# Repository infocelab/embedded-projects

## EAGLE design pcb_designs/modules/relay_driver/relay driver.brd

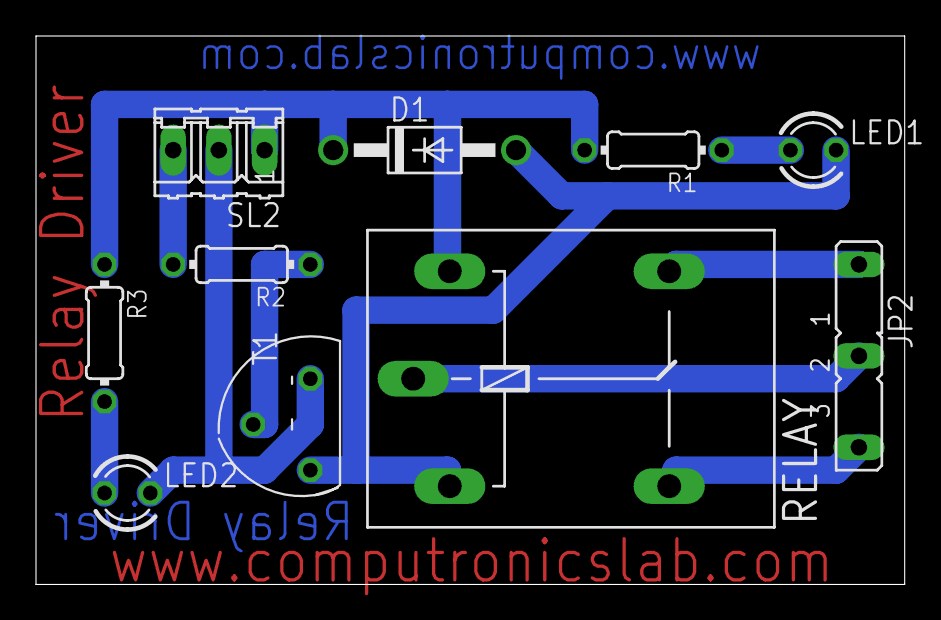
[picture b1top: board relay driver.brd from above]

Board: 2 copper layers, 48.3 x 30.5 mm, 10 parts (0 on the bottom side), 10 nets.

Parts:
D1: 1N4007; DO41-10
JP2: JP2
LED1, LED2: LED3MM
R1, R3: 330E; 0204/7
R2: 2.2K; 0204/7
RELAY: 12V; G5LE
SL2: 03P
T1: BC547; TO92

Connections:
unnamed: D1.A, LED1.K, RELAY.1, T1.3
unnamed: JP2.2, RELAY.P
unnamed: LED1.A, R1.1
unnamed: R2.1, T1.2
unnamed: LED2.K, SL2.2, T1.1
unnamed: D1.C, R1.2, R3.1, RELAY.2, SL2.1
unnamed: R2.2, SL2.3
unnamed: JP2.3, RELAY.S
unnamed: LED2.A, R3.2
unnamed: JP2.1, RELAY.O

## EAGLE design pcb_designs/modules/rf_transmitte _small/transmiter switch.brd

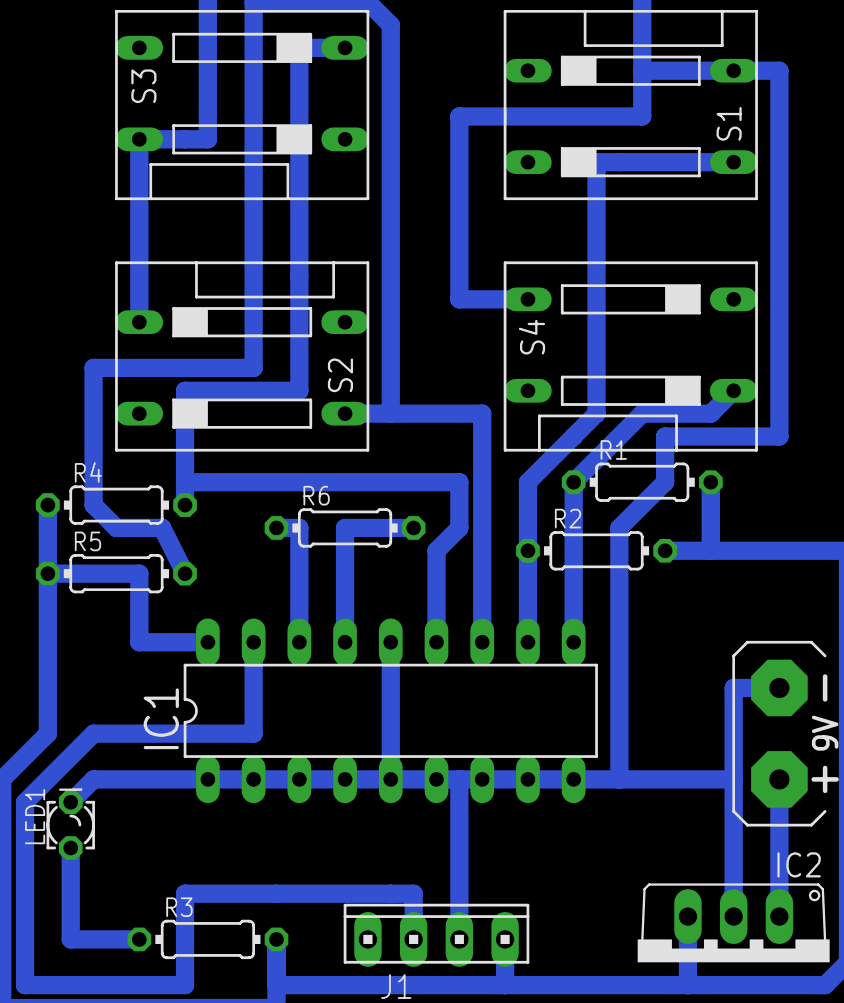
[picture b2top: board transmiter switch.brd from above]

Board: 2 copper layers, 15 parts (0 on the bottom side), 11 nets.

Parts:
G1: AB9V
IC1: HT12E; DIL18
IC2: 7805TV; TO220V
J1: transmitter; 10X04MTA
LED1: 5mm; LED_LD260
R1, R2, R4, R5: 1k; 0204/7
R3: 330E; 0204/7
R6: 1ME; 0204/7
S1: push switch 1; DS-02
S2: push switch2; DS-02
S3: push switch 3; DS-02
S4: push switch 4; DS-02

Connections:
unnamed: LED1.A, R3.1
unnamed: IC1.10, R1.1, S4.1
unnamed: IC1.11, R2.1, S1.3
unnamed: IC1.12, R5.2, S2.3
unnamed: IC1.13, R4.2, S3.2
unnamed: IC1.16, R6.1
unnamed: IC1.15, R6.2
unnamed: IC1.18, IC2.3, J1.1, R1.2, R2.2, R3.2, R4.1, R5.1
unnamed: IC1.17, J1.3
unnamed: G1.-, IC1.1, IC1.2, IC1.3, IC1.4, IC1.5, IC1.6, IC1.7, IC1.8, IC1.9, IC1.14, IC2.2, J1.2, LED1.K, S1.4, S2.1, S3.4, S4.3
unnamed: G1.+, IC2.1

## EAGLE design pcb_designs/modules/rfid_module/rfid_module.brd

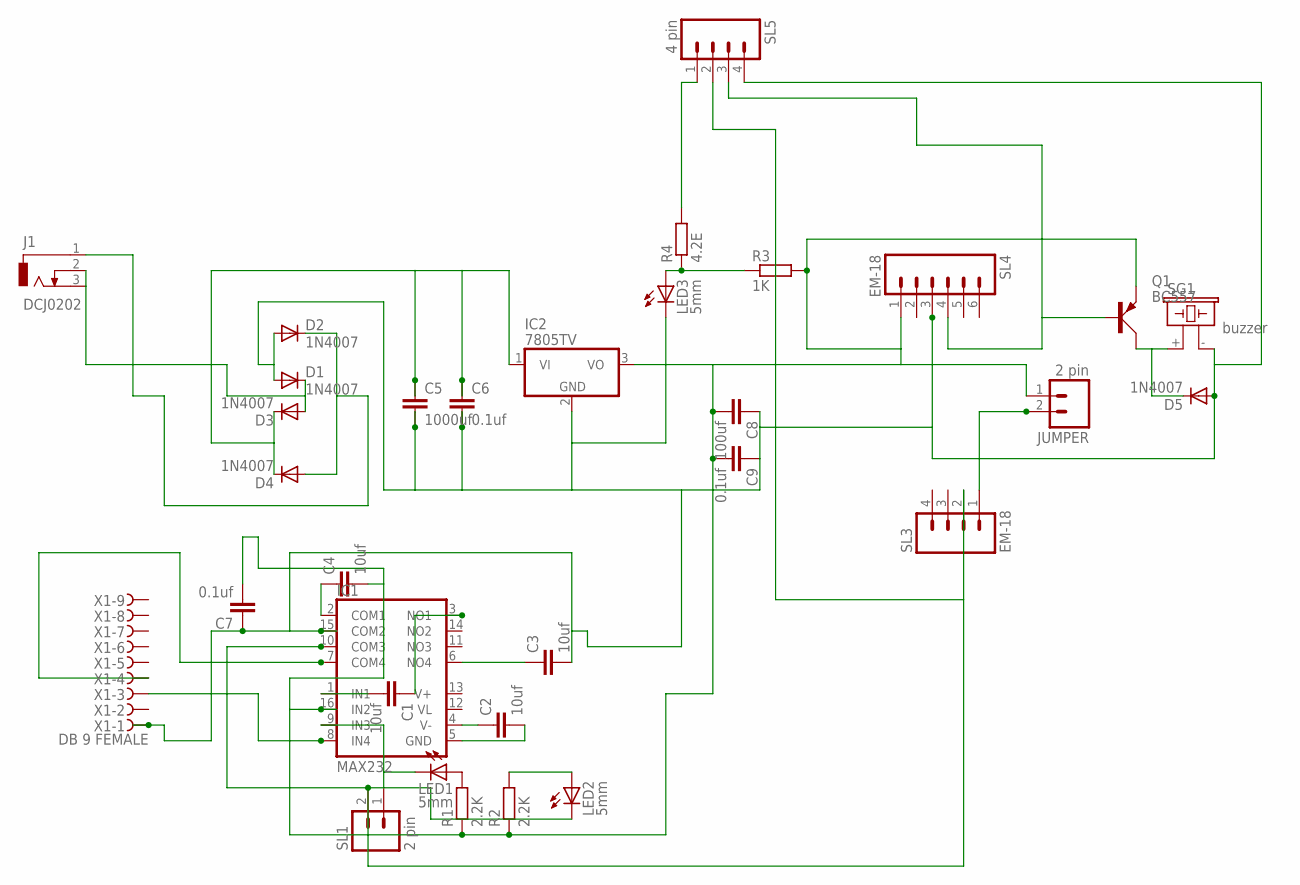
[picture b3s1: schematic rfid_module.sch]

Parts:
C1, C2, C3, C4: 10uf; C2.5-3
C5: 1000uf; C5B7.2
C6, C7, C9: 0.1uf; C2.5-3
C8: 100uf; C2.5-3
D1, D2, D3, D4, D5: 1N4007; DO41-10
IC1: MAX232; DIL16
IC2: 7805TV; TO220V
J1: DCJ0202
JUMPER: 2 pin; 02P
LED1, LED2, LED3: 5mm; LED5MM
Q1: BC557; SOT54A
R1, R2: 2.2K; 0204/7
R3: 1K; 0204/7
R4: 4.2E; 0204/7
SG1: buzzer; F/CM12P
SL1: 2 pin; 02P
SL3: EM-18; 04P
SL4: EM-18; 06P
SL5: 4 pin; 04P
X1: DB 9 FEMALE; H2M09ST

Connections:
unnamed: C1.2, IC1.1 (IN1)
unnamed: C1.1, IC1.3 (NO1)
unnamed: C2.1, IC1.4 (V-)
unnamed: C2.2, IC1.5 (GND)
unnamed: C3.1, IC1.6 (NO4)
unnamed: C4.2, C7.2, C8.2, C9.2, IC1.16 (IN2), IC2.3 (VO), JUMPER.1, Q1.E, R1.1, R2.1, R3.2, SL4.1
unnamed: C4.1, IC1.2 (COM1)
unnamed: IC1.9 (IN3), LED1.K (C), SL1.1
unnamed: IC1.8 (IN4), X1.3
unnamed: IC1.7 (COM4), X1.4
unnamed: IC1.10 (COM3), LED2.K (C), SL1.2, SL3.2, SL5.2
unnamed: LED2.A, R2.2
unnamed: C3.2, C5.2, C6.2, C7.1, C8.1, C9.1, D1.A, D2.A, D5.A, IC1.15 (COM2), IC2.2 (GND), LED3.K (C), SG1.- (2), SL4.3, SL5.4, X1.1
unnamed: C5.1, C6.1, D3.C, D4.C, IC2.1 (VI)
unnamed: D2.C, D4.A, J1.1
unnamed: LED1.A, R1.2
unnamed: D5.C, Q1.C, SG1.+ (1)
unnamed: D1.C, D3.A, J1.2, J1.3
unnamed: Q1.B, SL4.4, SL5.3
unnamed: JUMPER.2, SL3.1
unnamed: LED3.A, R3.1, R4.1
unnamed: R4.2, SL5.1
V+: IC1.13 (V+)
VL: IC1.12 (VL)

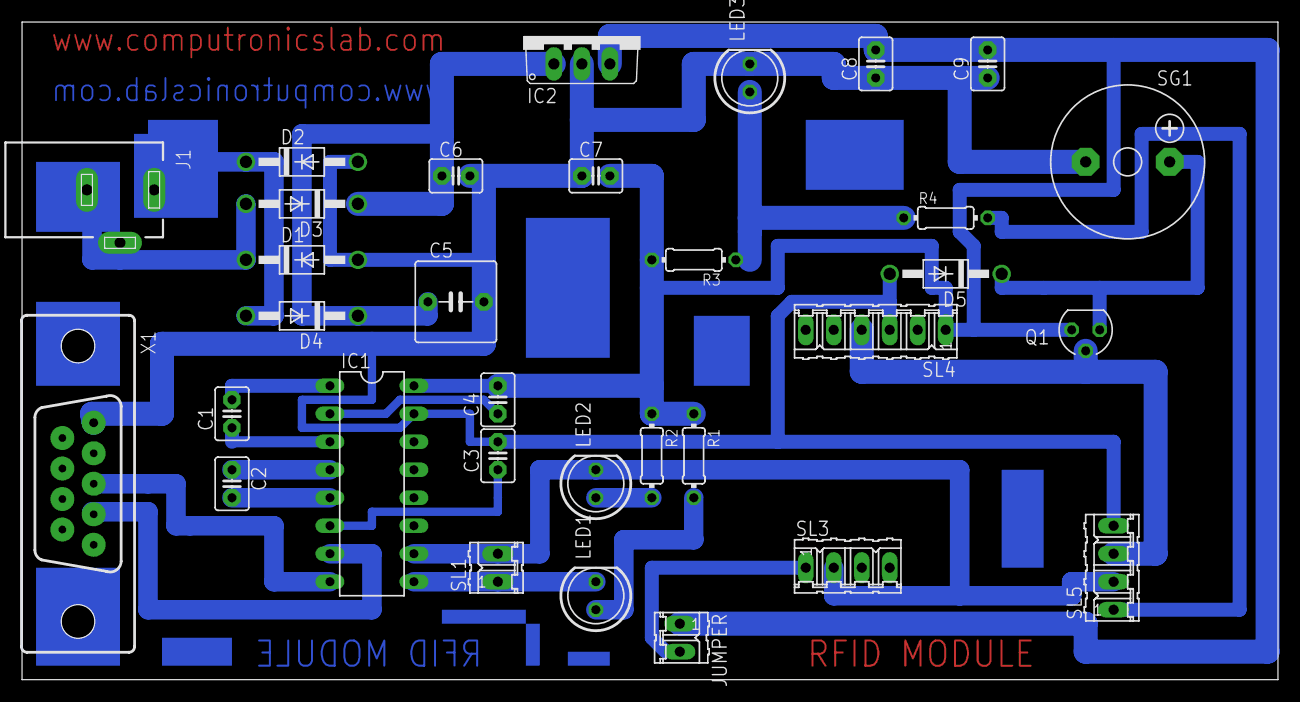
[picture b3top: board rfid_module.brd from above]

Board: 2 copper layers, 114.0 x 59.7 mm, 32 parts (0 on the bottom side), 22 nets.

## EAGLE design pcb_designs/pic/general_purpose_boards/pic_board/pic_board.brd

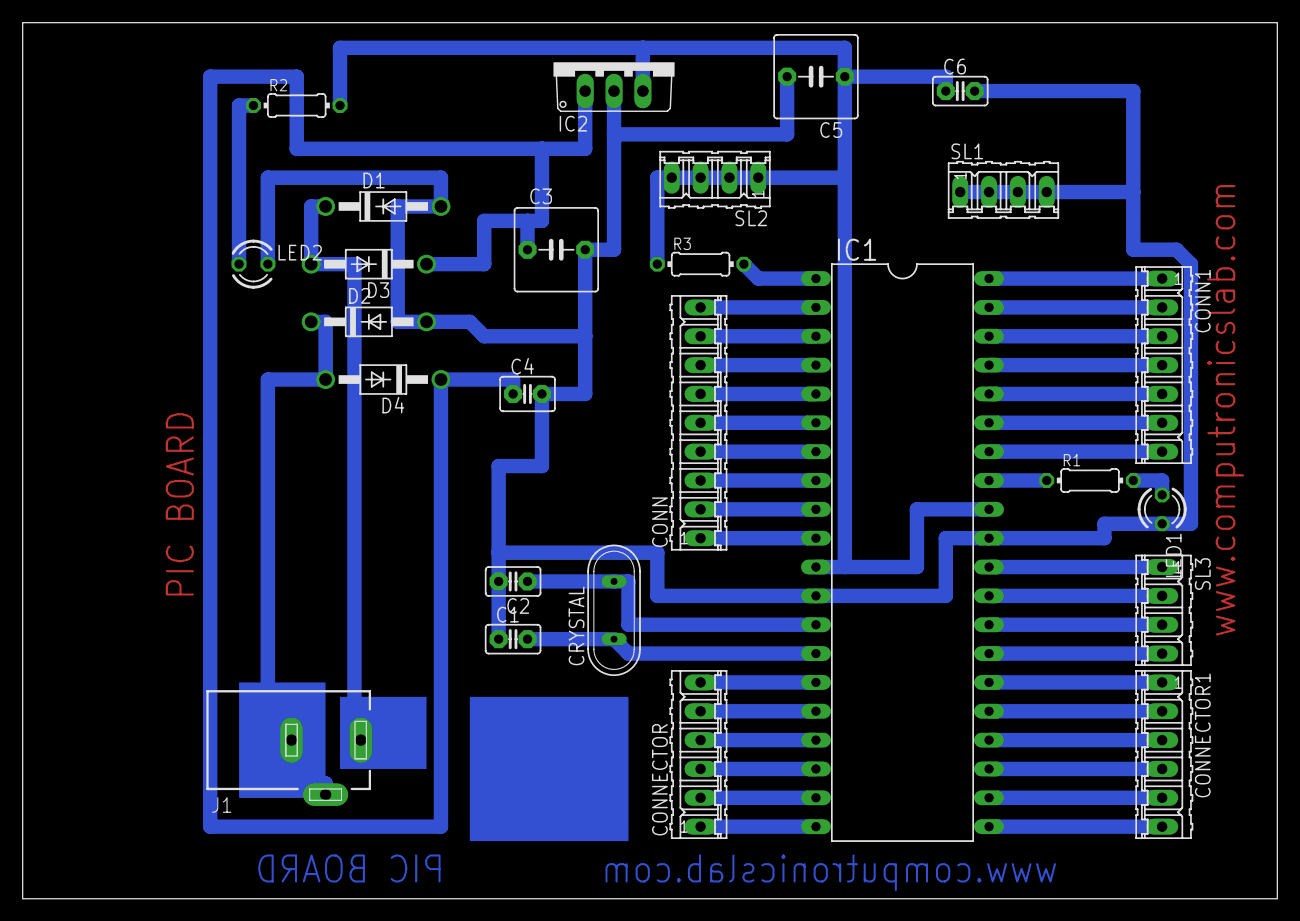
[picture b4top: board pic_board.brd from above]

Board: 2 copper layers, 110.5 x 77.1 mm, 26 parts (0 on the bottom side), 43 nets.

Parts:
C1, C2, C6: 22pf; C2.5-2
C3: 1000uf; C5B7.2
C4: 0.1uf; C2.5-3
C5: 100uf; C5B7.2
CONN: 9 pin; 09P
CONN1: 7 pin; 07P
CONNECTOR, CONNECTOR1: 6 pin; 06P
CRYSTAL: 8MHZ; QS
D1, D2, D3, D4: 1N4007; DO41-10
IC1: PIC16f877a; DIL40
IC2: 7805TV; TO220V
J1: DCJ0303
LED1, LED2: 3mm; LED3MM
R1, R2: 220E; 0204/7
R3: 10K; 0204/7
SL1, SL2, SL3: 4 pin; 04P

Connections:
unnamed: C2.1, CRYSTAL.2, IC1.13
unnamed: C1.2, CRYSTAL.1, IC1.14
unnamed: LED1.A, R1.2
unnamed: CONN.1, IC1.10
unnamed: CONN.2, IC1.9
unnamed: CONN.3, IC1.8
unnamed: CONN.4, IC1.7
unnamed: CONN.5, IC1.6
unnamed: CONN.6, IC1.5
unnamed: CONN.7, IC1.4
unnamed: CONN.8, IC1.3
unnamed: CONN.9, IC1.2
unnamed: CONNECTOR.1, IC1.20
unnamed: CONNECTOR.2, IC1.19
unnamed: CONNECTOR.3, IC1.18
unnamed: CONNECTOR.4, IC1.17
unnamed: CONNECTOR.5, IC1.16
unnamed: CONNECTOR.6, IC1.15
unnamed: CONN1.1, IC1.40
unnamed: CONN1.2, IC1.39
unnamed: CONN1.3, IC1.38
unnamed: CONN1.4, IC1.37
unnamed: CONN1.5, IC1.36
unnamed: CONN1.6, IC1.35
unnamed: CONN1.7, IC1.34
unnamed: CONNECTOR1.1, IC1.26
unnamed: CONNECTOR1.2, IC1.25
unnamed: CONNECTOR1.3, IC1.24
unnamed: IC1.33, R1.1
unnamed: C3.1, C4.1, D3.C, D4.C, IC2.1
unnamed: D2.C, D4.A, J1.2, J1.3
unnamed: D1.C, D3.A, J1.1
unnamed: C5.1, C6.1, IC1.11, IC1.32, IC2.3, R2.2, R3.1, SL2.1, SL2.2, SL2.3, SL2.4
unnamed: LED2.A, R2.1
unnamed: C1.1, C2.2, C3.2, C4.2, C5.2, C6.2, D1.A, D2.A, IC1.12, IC1.31, IC2.2, LED1.K, LED2.K, SL1.1, SL1.2, SL1.3, SL1.4
unnamed: CONNECTOR1.4, IC1.23
unnamed: CONNECTOR1.5, IC1.22
unnamed: CONNECTOR1.6, IC1.21
unnamed: IC1.1, R3.2
unnamed: IC1.30, SL3.1
unnamed: IC1.29, SL3.2
unnamed: IC1.28, SL3.3
unnamed: IC1.27, SL3.4

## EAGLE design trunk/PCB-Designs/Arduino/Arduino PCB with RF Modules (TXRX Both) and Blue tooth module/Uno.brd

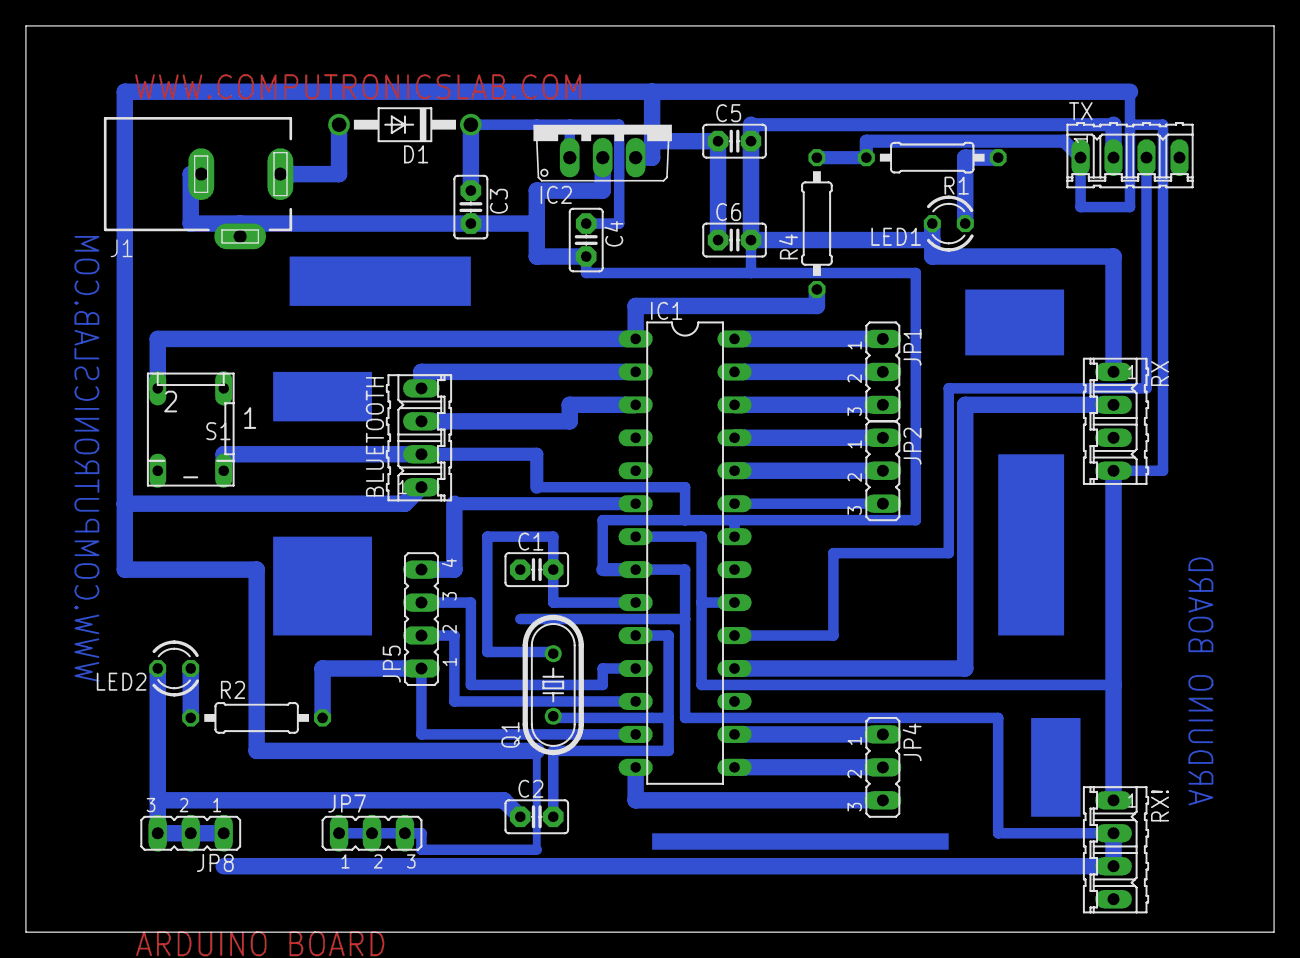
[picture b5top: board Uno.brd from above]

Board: 2 copper layers, 96.2 x 69.8 mm, 27 parts (0 on the bottom side), 26 nets.

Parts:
BLUETOOTH: 04P
C1, C2: 22pf; C2.5-2
C3: 470UF; C2.5-2
C4, C5: 0.1uf; C2.5-2
C6: 4.7uf; C2.5-2
D1: 1N4007; DO41-10
IC1: ATMEGA328; DIL28-3
IC2: 7805; TO220V
J1: DCJ0303
JP1, JP2, JP4, JP7, JP8: JP2
JP5: JP4
LED1, LED2: LED3MM
Q1: 12MHZ; HC49/S
R1: 220R; 0207/10
R2: 330R; 0207/10
R4: 10K; 0207/10
RX: 04P
RX!: 04P
S1: DP-02
TX: 04P

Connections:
unnamed: C1.2, IC1.9, Q1.2
unnamed: C2.2, IC1.10, Q1.1
unnamed: D1.A, J1.1
unnamed: BLUETOOTH.1, C5.1, C6.1, IC1.7, IC1.20, IC2.3, JP7.1, JP7.2, JP7.3, R1.2, R4.2, RX.4, RX!.1, TX.1
unnamed: BLUETOOTH.2, C1.1, C2.1, C3.2, C4.2, C5.2, C6.2, IC1.8, IC1.22, IC2.2, J1.2, J1.3, JP8.1, JP8.2, JP8.3, LED1.K, LED2.K, RX.1, RX!.2, RX!.3, S1.4, TX.2
unnamed: LED1.A, R1.1
unnamed: C3.1, C4.1, D1.C, IC2.1
unnamed: IC1.28, JP1.1
unnamed: IC1.27, JP1.2
unnamed: IC1.26, JP1.3
unnamed: IC1.25, JP2.1
unnamed: IC1.24, JP2.2
unnamed: IC1.23, JP2.3
unnamed: BLUETOOTH.4, IC1.2
unnamed: BLUETOOTH.3, IC1.3
unnamed: IC1.6, JP5.4
unnamed: IC1.12, JP5.2
unnamed: IC1.11, JP5.3
unnamed: IC1.13, JP5.1, R2.2
unnamed: IC1.14, JP4.3
unnamed: IC1.15, JP4.2
unnamed: IC1.16, JP4.1
unnamed: IC1.18, RX.2
unnamed: IC1.19, TX.3
unnamed: IC1.1, R4.1, S1.2
unnamed: LED2.A, R2.1

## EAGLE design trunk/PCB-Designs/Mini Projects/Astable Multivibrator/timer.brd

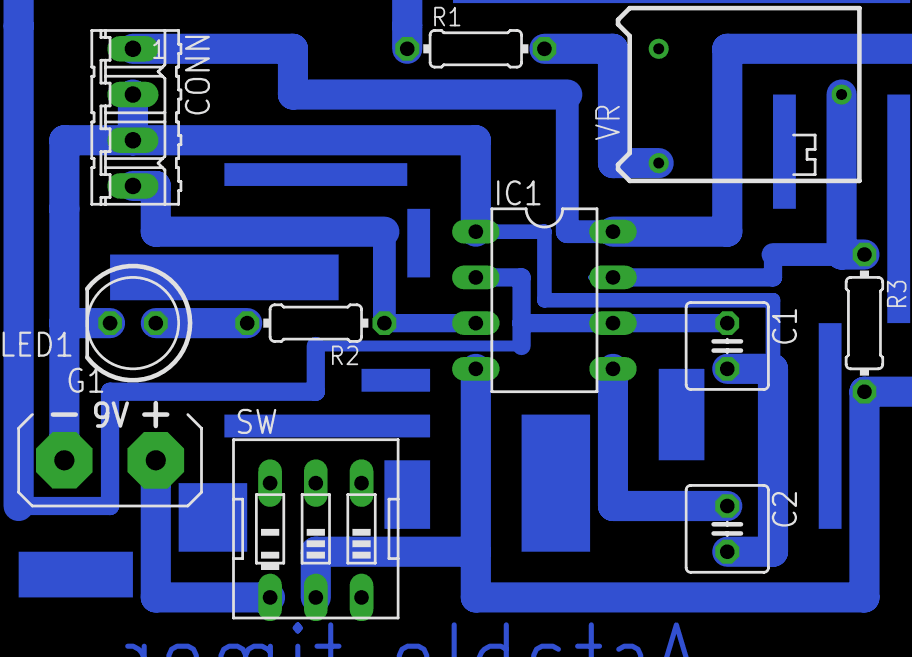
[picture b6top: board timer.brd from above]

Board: 2 copper layers, 11 parts (0 on the bottom side), 9 nets.

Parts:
C1: 100uf; C025-050X050
C2: 0.1uf; C025-050X050
CONN: 4 PIN; 04P
G1: AB9V
IC1: NE555; DIL-08
LED1: 5mm; LED5MM
R1: 1K; 0204/7
R2: 220E; 0204/7
R3: 4.7K; 0204/7
SW: on/of button; EDG-03
VR: 100k; RTRIM64P

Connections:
unnamed: C1.1, IC1.2, IC1.6, R1.1
unnamed: C2.1, IC1.5
unnamed: IC1.7, R3.1, VR.2
unnamed: CONN.4, IC1.3, R2.1
unnamed: LED1.A, R2.2
unnamed: G1.+, SW.1
unnamed: R1.2, VR.1
unnamed: C1.2, C2.2, CONN.2, CONN.3, G1.-, IC1.1, LED1.K
unnamed: CONN.1, IC1.4, IC1.8, R3.2, SW.2

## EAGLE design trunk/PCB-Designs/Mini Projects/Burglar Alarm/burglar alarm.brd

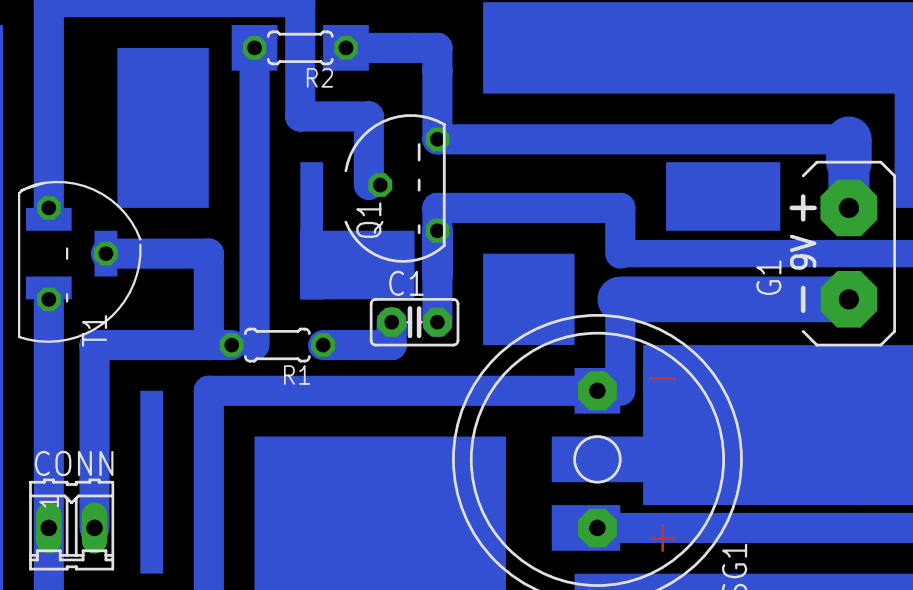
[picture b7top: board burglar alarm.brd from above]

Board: 2 copper layers, 8 parts (0 on the bottom side), 6 nets.

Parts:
C1: 0.1UF; C2.5-2
CONN: 2 PIN; 02P
G1: AB9V
Q1: BC557; TO92
R1, R2: 10k; 0204/5
SG1: BUZZER; F/QMB
T1: BC547; TO92

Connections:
unnamed: C1.2, Q1.3, SG1.+
unnamed: C1.1, R1.1
unnamed: CONN.1, G1.-, SG1.-, T1.1
unnamed: CONN.2, R1.2, R2.2, T1.2
unnamed: G1.+, Q1.1, R2.1
unnamed: Q1.2, T1.3

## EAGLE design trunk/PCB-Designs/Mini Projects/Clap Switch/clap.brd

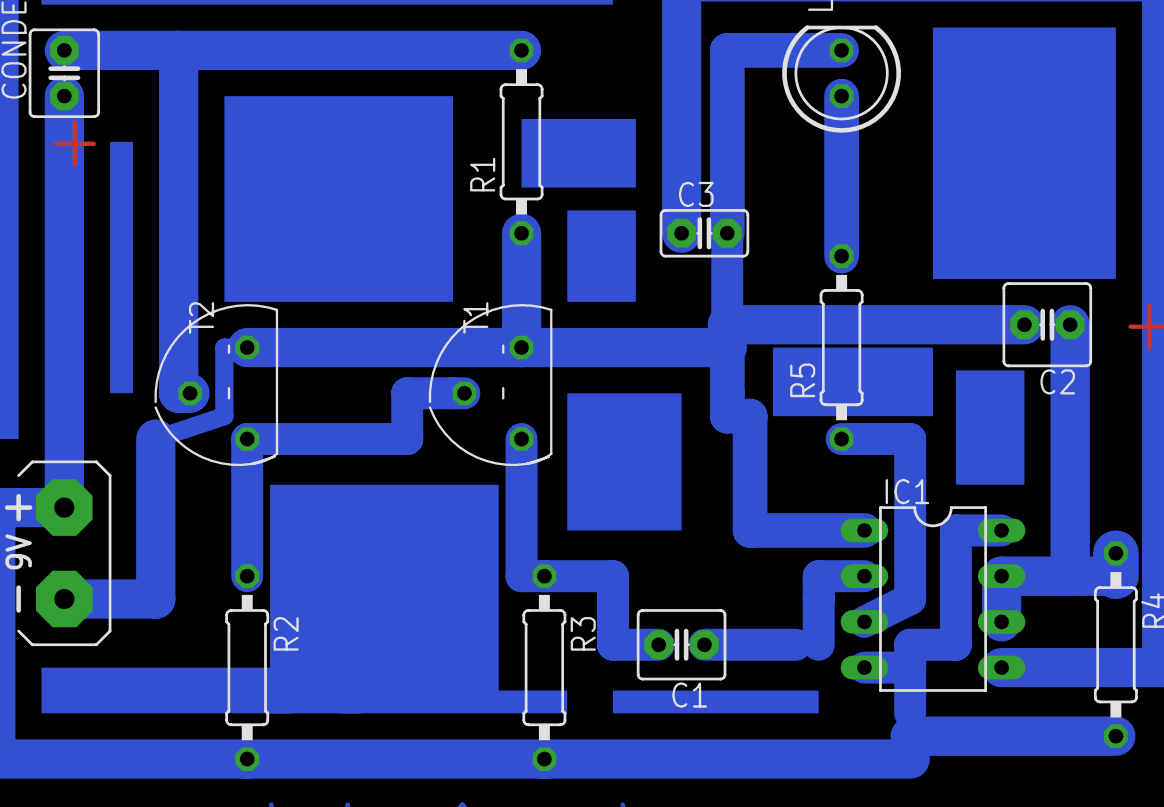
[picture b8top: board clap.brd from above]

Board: 2 copper layers, 14 parts (0 on the bottom side), 10 nets.

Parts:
C1: 104 (.1uf); C2.5-4
C2: 100uf; C2.5-5
C3: 104; C2.5-2
CONDENSERMIC: C2.5-4
G1: AB9V
IC1: NE555; DIL-08
LED1: 5MM; LED5MM
R1: 4.7k; 0207/10
R2: 1k; 0207/10
R3: 470k; 0207/10
R4: 47k; 0207/10
R5: 330 R; 0207/10
T1, T2: BC547; TO92

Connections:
unnamed: R2.1, T1.2, T2.3
unnamed: C1.2, R3.1, T1.3
unnamed: C2.1, IC1.6, IC1.7, R4.1
unnamed: CONDENSERMIC.1, G1.+, IC1.4, IC1.8, R2.2, R3.2, R4.2
unnamed: CONDENSERMIC.2, R1.2, T2.2
unnamed: C3.1, IC1.5
unnamed: LED1.A, R5.2
unnamed: C2.2, C3.2, G1.-, IC1.1, LED1.K, R1.1, T1.1, T2.1
unnamed: C1.1, IC1.2
unnamed: IC1.3, R5.1
